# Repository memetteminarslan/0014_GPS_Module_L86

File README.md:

# 0014_GPS_Module_L86
You are seeing a large number of widely used GPS modules in electronic development kits. More information coming soon...

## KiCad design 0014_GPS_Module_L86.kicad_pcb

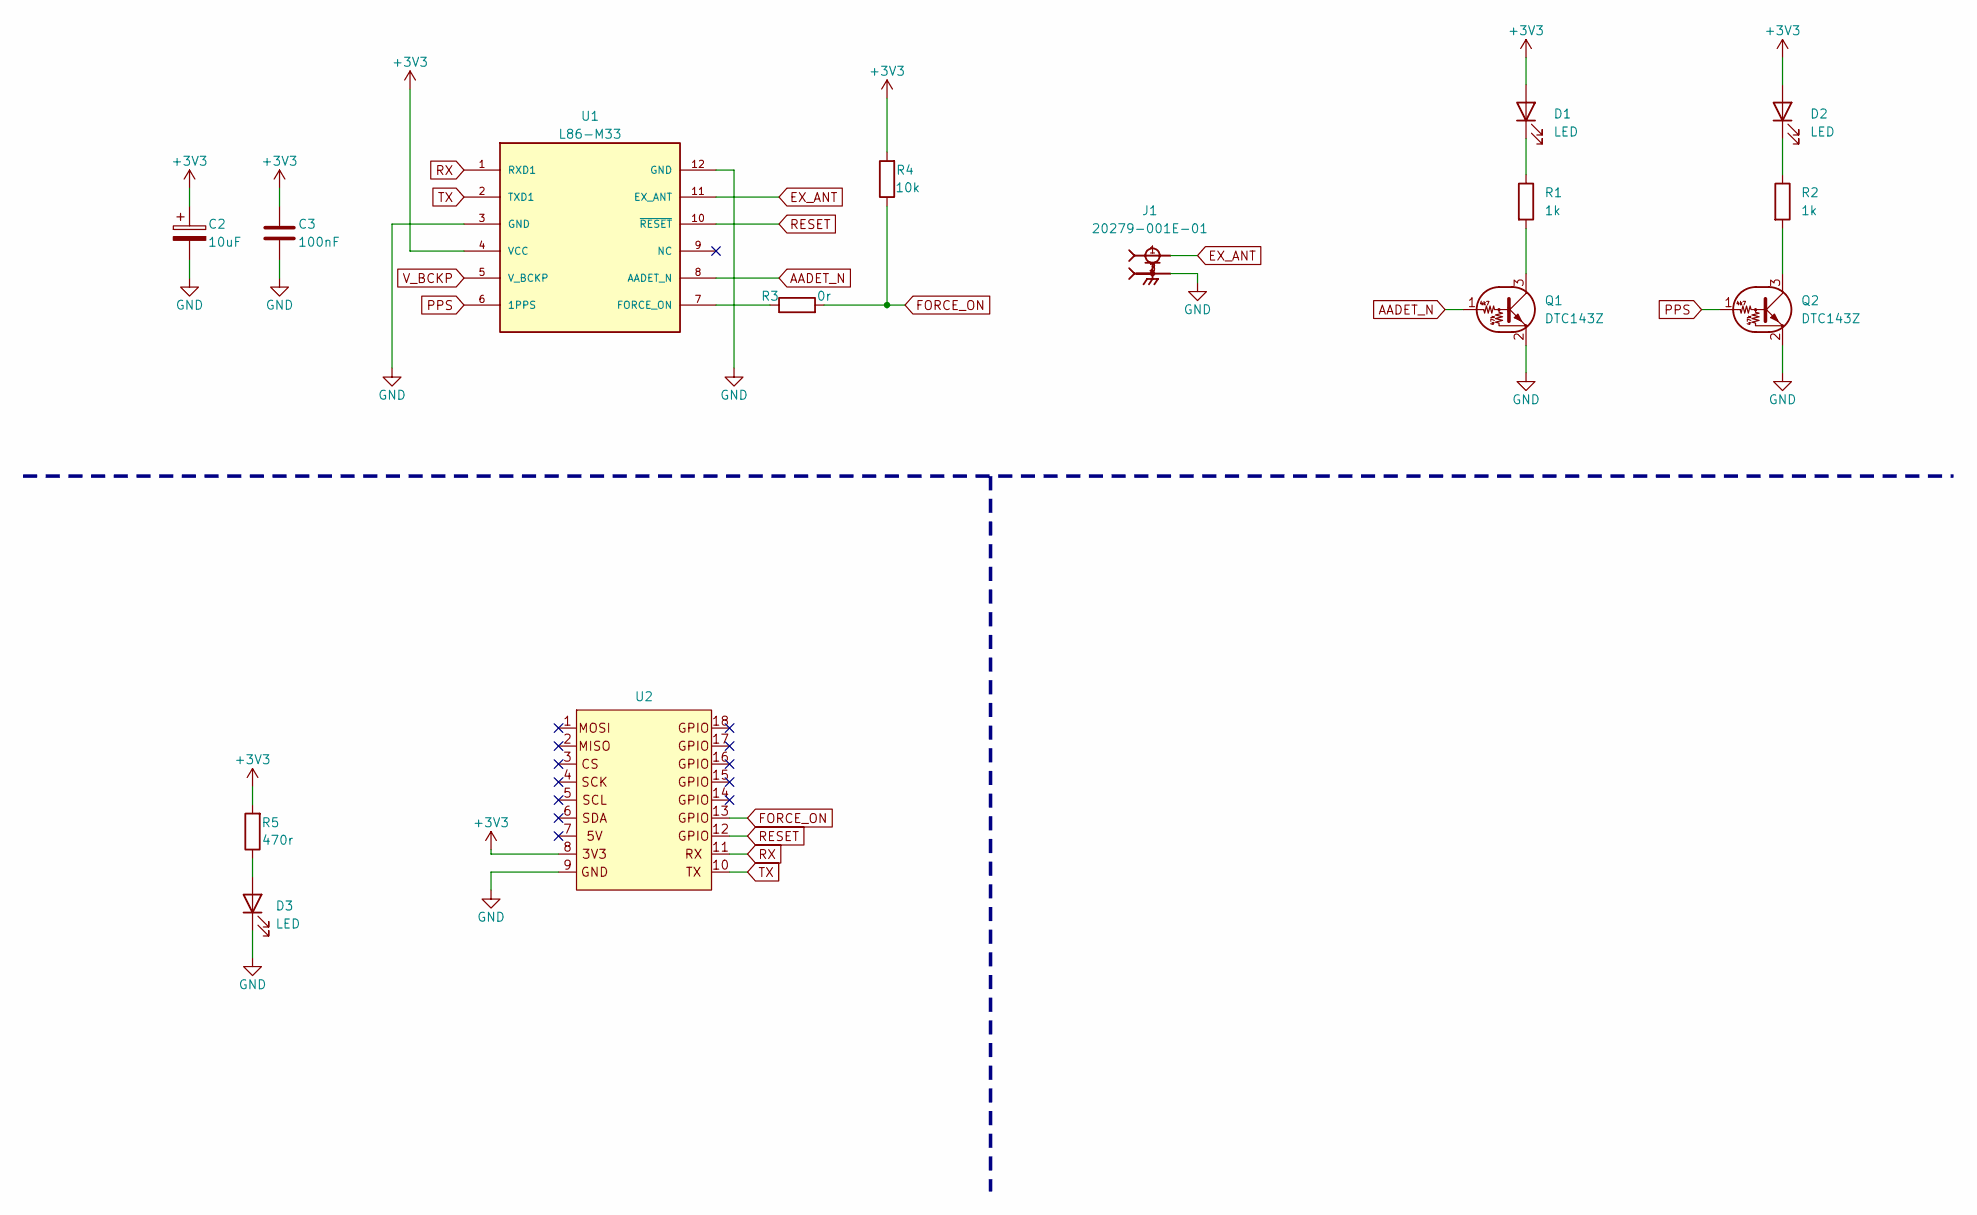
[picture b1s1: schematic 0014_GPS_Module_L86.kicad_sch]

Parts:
C2: 10uF; CP_EIA-2012-12_Kemet-R
C3: 100nF; C_0603_1608Metric
D1, D2, D3: LED; LED_0603_1608Metric
J1: 20279-001E-01; L-KLS1-IPEX-20279-001E-0; PARTREV 21
Q1, Q2: DTC143Z; SOT-323_SC-70
R1, R2: 1k; R_0603_1608Metric
R3: 0r; R_0603_1608Metric
R4: 10k; R_0603_1608Metric
R5: 470r; R_0603_1608Metric
U1: L86-M33; XCVR_L86-M33
U2: pin_header

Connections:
+3V3: C2.1, C3.1, D1.2 (A), D2.2 (A), R4.2, R5.2, U1.4 (VCC), U2.8
AADET_N: Q1.1 (B), U1.8 (AADET_N)
EX_ANT: J1.1, U1.11 (EX_ANT)
FORCE_ON: R3.2, R4.1, U2.13
GND: C2.2, C3.2, D3.1 (K), J1.2, J1.3, Q1.2 (E), Q2.2 (E), U1.3 (GND), U1.12 (GND), U2.9
unnamed: D1.1 (K), R1.1
unnamed: D2.1 (K), R2.1
unnamed: D3.2 (A), R5.1
unnamed: Q1.3 (C), R1.2
unnamed: Q2.3 (C), R2.2
unnamed: R3.1, U1.7 (FORCE_ON)
PPS: Q2.1 (B), U1.6 (1PPS)
RESET: U1.10 (~RESET), U2.12
RX: U1.1 (RXD1), U2.11
TX: U1.2 (TXD1), U2.10
V_BCKP: U1.5 (V_BCKP)

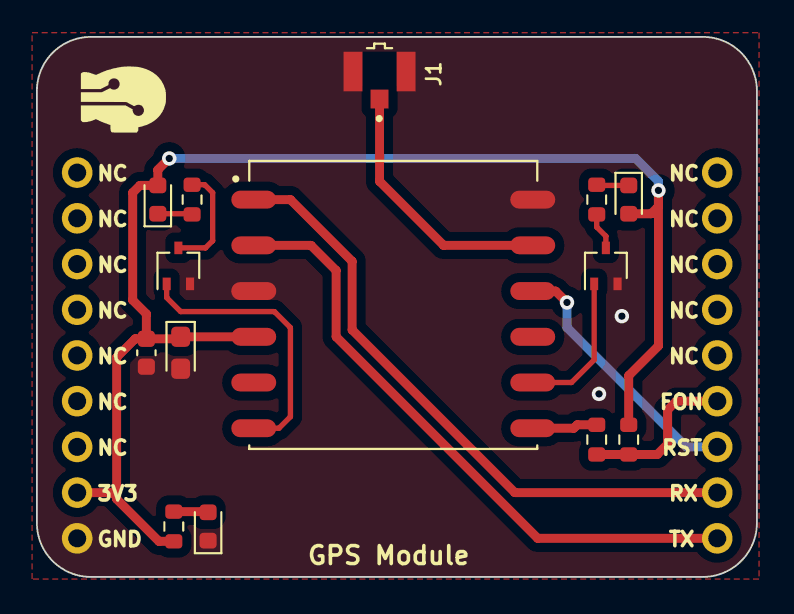
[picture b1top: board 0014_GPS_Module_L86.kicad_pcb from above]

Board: 2 copper layers, 40.0 x 30.0 mm, 15 parts (0 on the bottom side), 15 nets.
